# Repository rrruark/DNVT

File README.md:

# DNVT
Digital Non-secure Voice Terminal Test Code and Switch PCBA Design Files.

http://robruark.com/projects/DNVT/DNVT_overview.html

This repo contains the PCBA design files for the DNVT test interface boards, four phone switches which run Nick Andre's code, and the crappy support code I wrote to initially reverse engineering DNVTs. 

The Arduino code encodes and decodes Differential Manchester, and the Python scripts determine the codewords. There is also a Python script which decodes differential manchester based on a CSV capture from an oscilloscope. Example files are provided.

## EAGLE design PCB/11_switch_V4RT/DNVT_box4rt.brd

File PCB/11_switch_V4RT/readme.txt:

Eagle Schematic: DNVT_box3rt.sch
Eagle Layout: DNVT_box3rt.brd
Schematic PDF: DNVT_box3rt.pdf

JLCPCB Gerbers: DNVT_box3rt_2023-05-02.zip
JLCPCB Top Placement: DNVT_box3rt_top_cpl.csv
JLCPCB BOM: DNVT_box3rt_top_bom.csv

Through Hole BOM: DNVT_box3rt_th_bom.csv
Additional BOM: DNVT_box3r_aux_bom.csv

Notes:

-The JLCPCB BOM maps all surface mount parts and all through hole parts aside from the DC barrel jack and transformers to parts available in JLCPCB's parts library.
-The bottom side parts are optional (additional chassis ground to Pico Ground capacitors and uSD card holder)
-The Digikey BOM lists through hole parts (DC barrel jack and transformers) which must be manually assembled.
-The additional BOM lists parts not captured in the Eagle BOM export: the case, OLED screen, Front and back plates, screws, nuts, cable for screen, and 48V power supply.

Designer Contact: Robert Ruark: rob@robruark.com

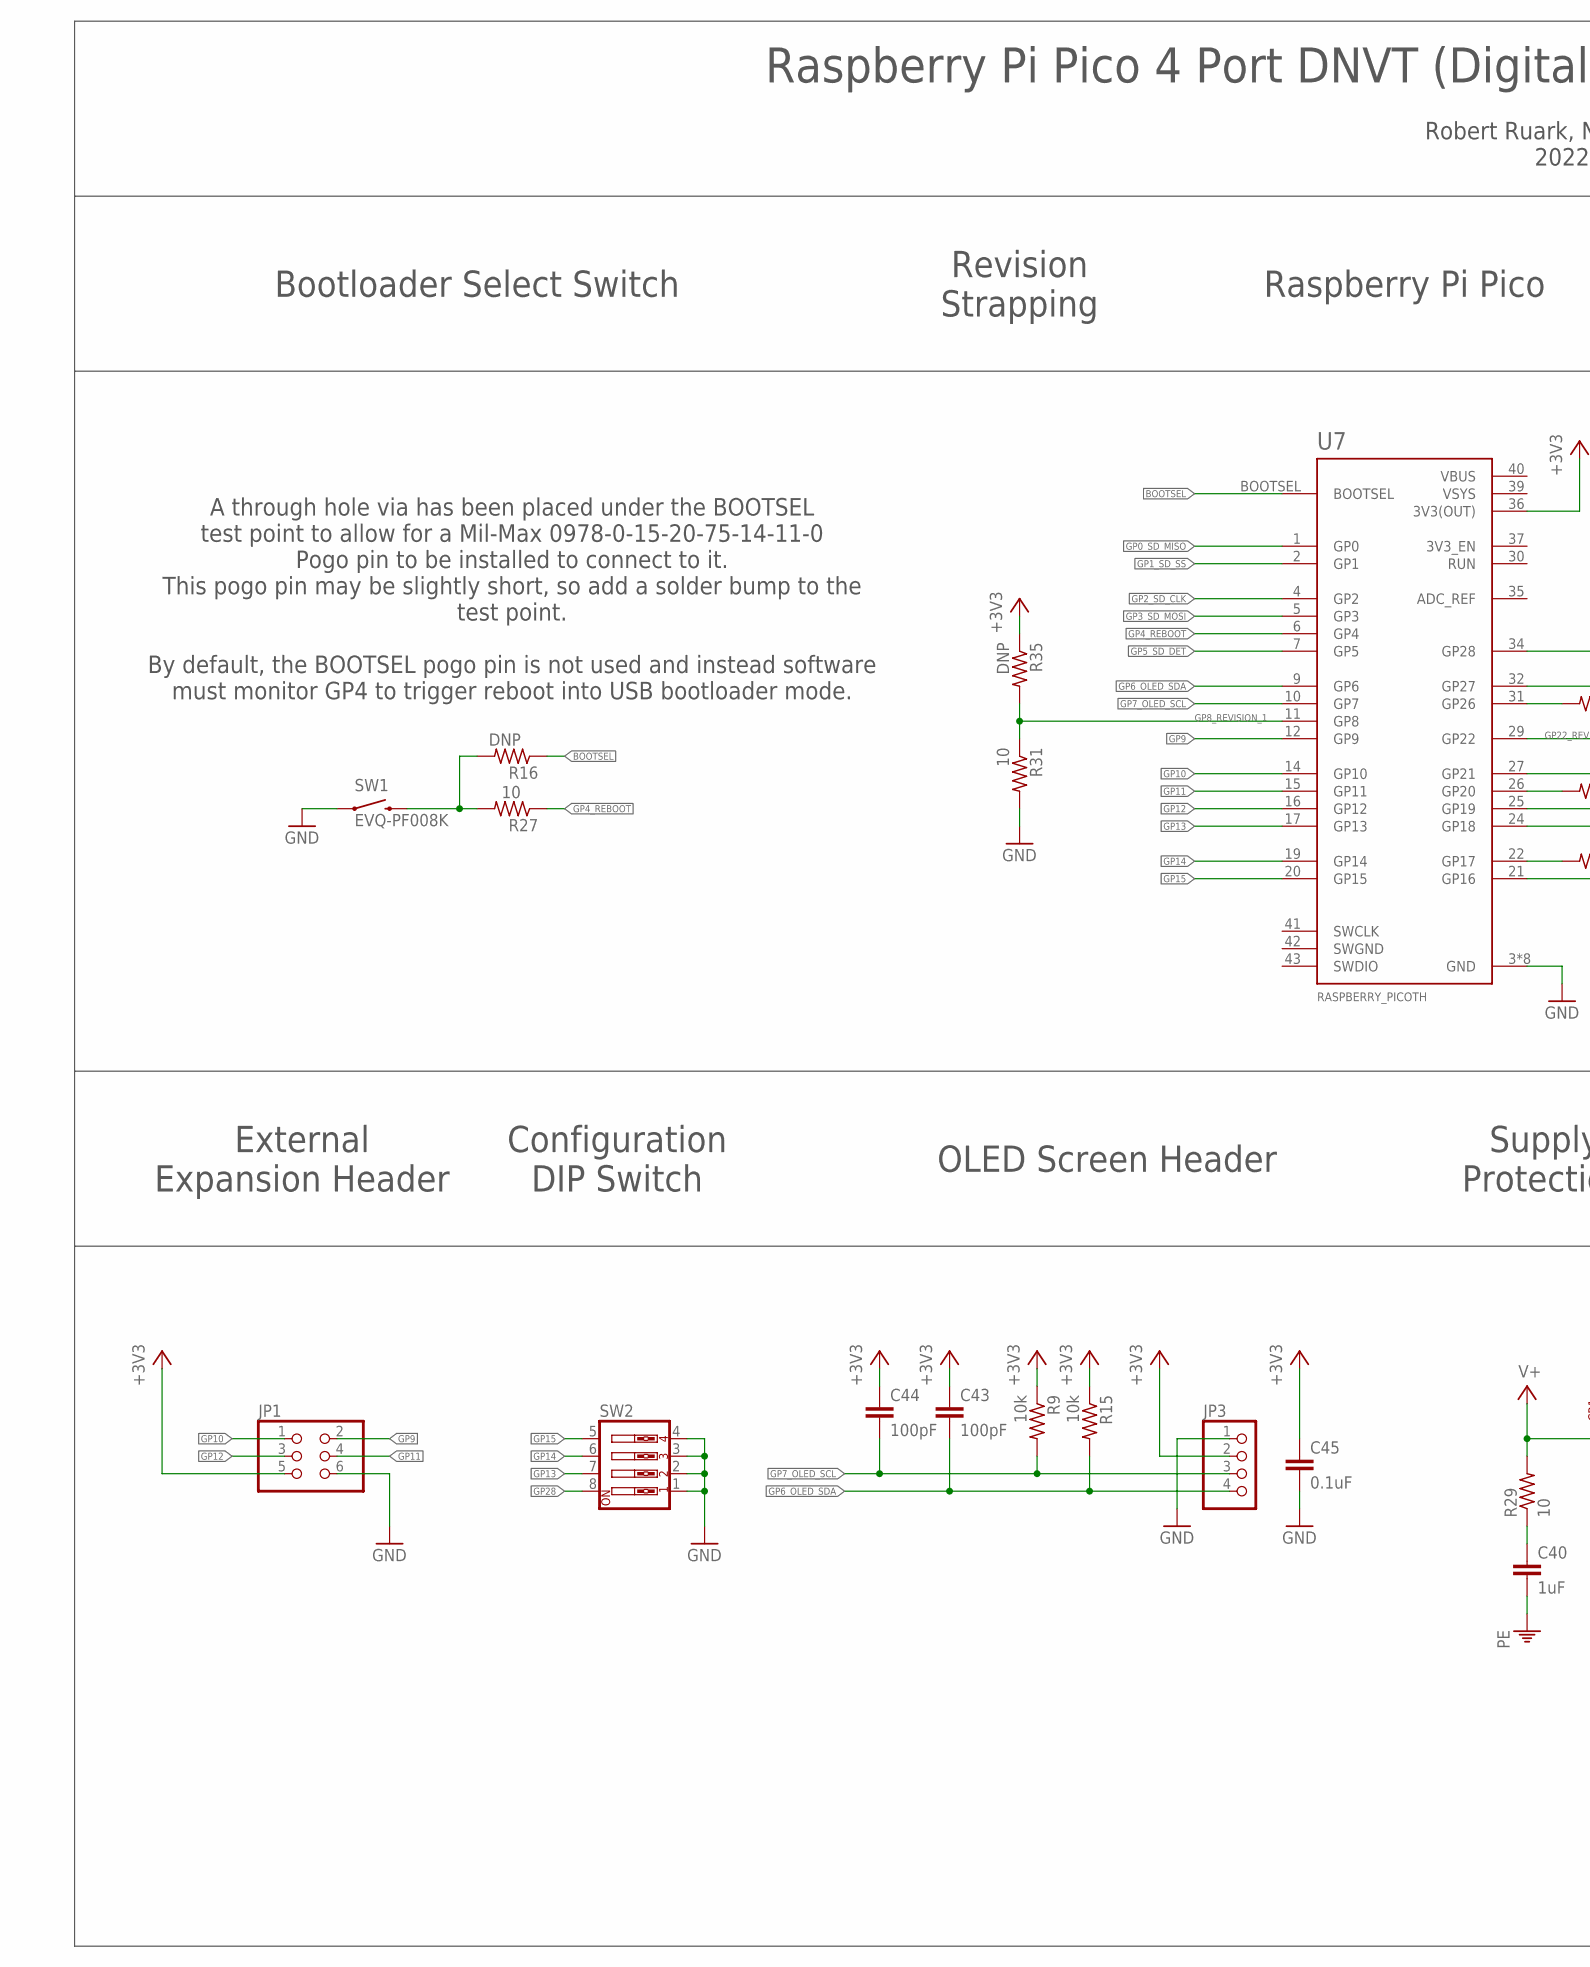
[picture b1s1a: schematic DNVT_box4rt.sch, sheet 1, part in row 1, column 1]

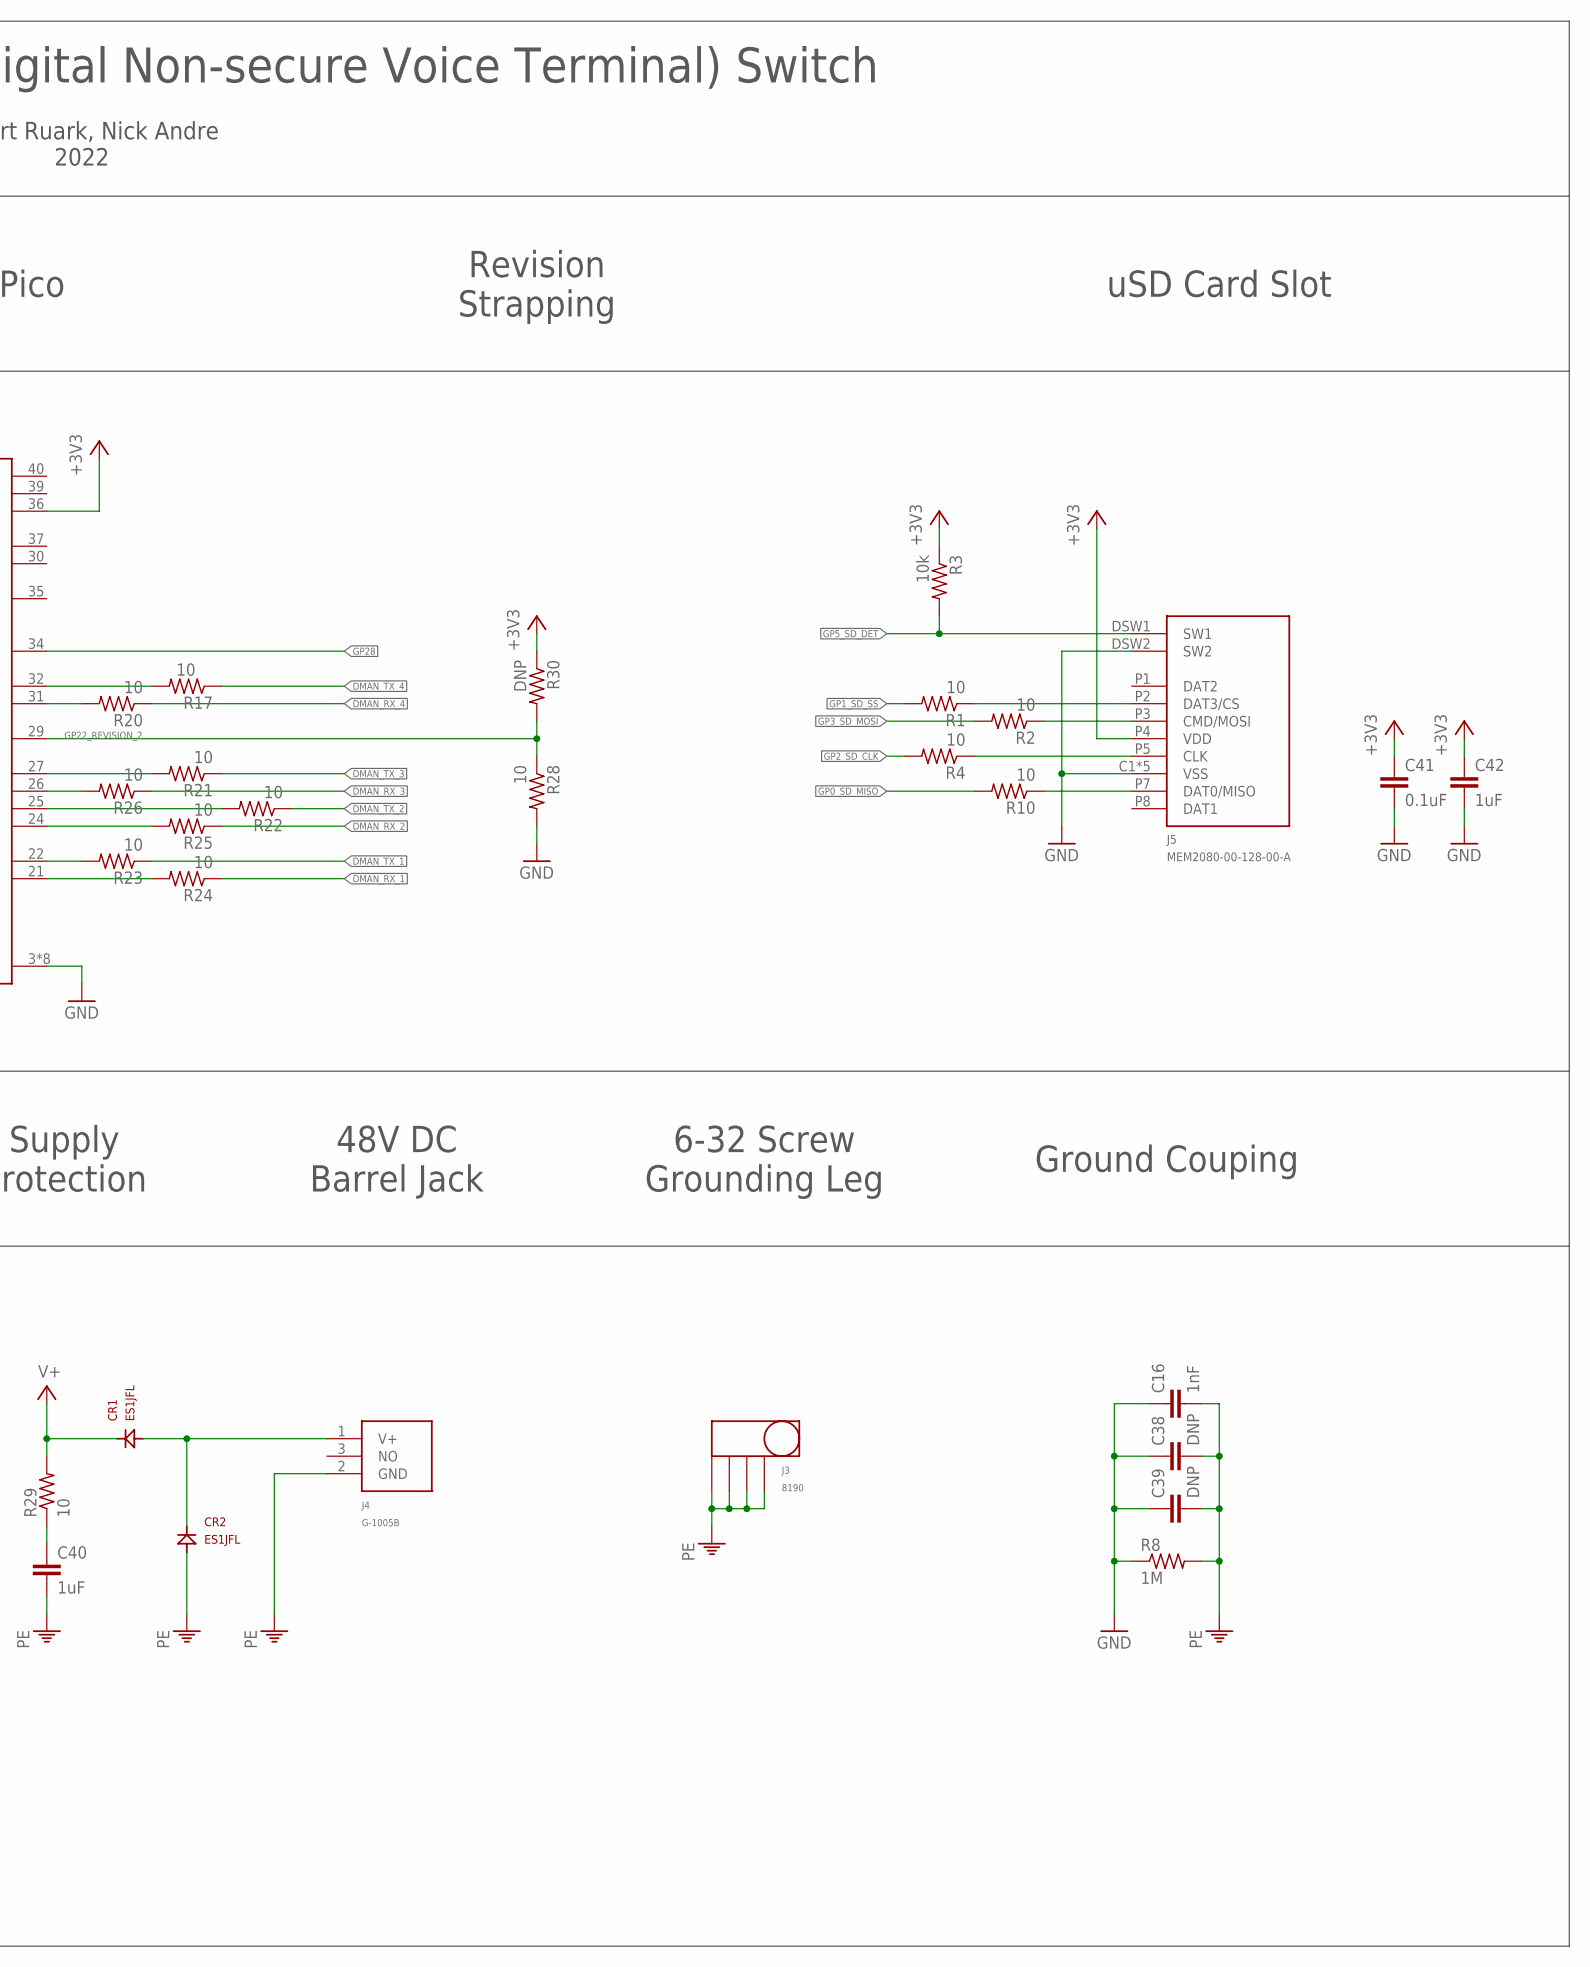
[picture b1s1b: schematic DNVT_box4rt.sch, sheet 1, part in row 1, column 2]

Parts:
C16: 1nF; 1206
C38, C39: DNP; 1206
C40: 1uF; 1206
C41, C45: 0.1uF; 0603
C42: 1uF; 0805
C43, C44: 100pF; 0603
CR1, CR2: ES1JFL; SOD123(AK)
J3: 8190; 7781
J4: G-1005B
J5: MEM2080-00-128-00-A; MEM2080
JP1: PINHD-2X3/90; 2X03/90
JP3: PINHD-1X4; 1X04
R1, R2, R4, R10, R17, R20, R21, R22, R23, R24, R25, R26, R27, R28, R31: 10; 0603
R3, R9, R15: 10k; 0603
R8: 1M; 1206
R16, R30, R35: DNP; 0603
R29: 10; 1206
SW1: EVQ-PF008K
SW2: SW_DIP-4; EDG-04
U7: RASPBERRY_PICOTH; PICO-PKG-TH

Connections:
+3V3: C41.1, C42.1, C43.1, C44.1, C45.1, J5.P4 (VDD), JP1.5, JP3.2, R3.1, R9.1, R15.1, R30.1, R35.1, U7.36 (3V3(OUT)); also elsewhere on the board
BOOTSEL: R16.1, U7.BOOTSEL
DMAN_RX_1: R24.1; also elsewhere on the board
DMAN_RX_2: R25.1; also elsewhere on the board
DMAN_RX_3: R26.1; also elsewhere on the board
DMAN_RX_4: R20.1; also elsewhere on the board
DMAN_TX_1: R23.1; also elsewhere on the board
DMAN_TX_2: R22.1; also elsewhere on the board
DMAN_TX_3: R21.1; also elsewhere on the board
DMAN_TX_4: R17.1; also elsewhere on the board
GND: C16.1, C38.1, C39.1, C41.2, C42.2, C45.2, J5.C1 (VSS), J5.C2 (VSS), J5.C3 (VSS), J5.C4 (VSS), J5.DSW2 (SW2), J5.P6 (VSS), JP1.6, JP3.1, R8.1, R28.2, R31.2, SW1.S1 (1), SW2.1, SW2.2, SW2.3, SW2.4, U7.3 (GND), U7.8 (GND), U7.13 (GND), U7.18 (GND), U7.23 (GND), U7.28 (GND), U7.33 (GND), U7.38 (GND); also elsewhere on the board
GP0_SD_MISO: R10.2, U7.1 (GP0)
GP1_SD_SS: R1.2, U7.2 (GP1)
GP2_SD_CLK: R4.2, U7.4 (GP2)
GP3_SD_MOSI: R2.2, U7.5 (GP3)
GP4_REBOOT: R27.1, U7.6 (GP4)
GP5_SD_DET: J5.DSW1 (SW1), R3.2, U7.7 (GP5)
GP6_OLED_SDA: C43.2, JP3.4, R15.2, U7.9 (GP6)
GP7_OLED_SCL: C44.2, JP3.3, R9.2, U7.10 (GP7)
GP8_REVISION_1: R31.1, R35.2, U7.11 (GP8)
GP9: JP1.2, U7.12 (GP9)
GP10: JP1.1, U7.14 (GP10)
GP11: JP1.4, U7.15 (GP11)
GP12: JP1.3, U7.16 (GP12)
GP13: SW2.7, U7.17 (GP13)
GP14: SW2.6, U7.19 (GP14)
GP15: SW2.5, U7.20 (GP15)
GP22_REVISION_2: R28.1, R30.2, U7.29 (GP22)
GP28: SW2.8, U7.34 (GP28)
unnamed: R20.2, U7.31 (GP26)
unnamed: R17.2, U7.32 (GP27)
unnamed: R24.2, U7.21 (GP16)
unnamed: R23.2, U7.22 (GP17)
unnamed: R16.2, R27.2, SW1.S2 (2)
unnamed: CR1.A, CR2.K, J4.1 (V+)
unnamed: R25.2, U7.24 (GP18)
unnamed: R22.2, U7.25 (GP19)
unnamed: R21.2, U7.27 (GP21)
unnamed: R26.2, U7.26 (GP20)
unnamed: J5.P5 (CLK), R4.1
unnamed: C40.1, R29.1
unnamed: J5.P7 (DAT0/MISO), R10.1
unnamed: J5.P3 (CMD/MOSI), R2.1
unnamed: J5.P2 (DAT3/CS), R1.1
PE: C16.2, C38.2, C39.2, C40.2, CR2.A, J3.P$1, J3.P$2, J3.P$3, J3.P$4, J4.2 (GND), R8.2; also elsewhere on the board
SWGND: U7.42 (SWGND)
V+: CR1.K, R29.2; also elsewhere on the board
VBUS: U7.40 (VBUS)
VSYS: U7.39 (VSYS)

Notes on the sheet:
Raspberry Pi Pico 4 Port DNVT (Digital Non-secure Voice Terminal) Switch
Robert Ruark, Nick Andre 2022
Raspberry Pi Pico
Ground Couping
External Expansion Header
OLED Screen Header
48V DC Barrel Jack
6-32 Screw Grounding Leg
A through hole via has been placed under the BOOTSEL test point to allow for a Mil-Max 0978-0-15-20-75-14-11-0 Pogo pin to be installed to connect to it. This pogo pin may be slightly short, so add a solder bump to the test point. By default, the BOOTSEL pogo pin is not used and instead software mu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
Configuration DIP Switch
Supply Protection
Revision Strapping
Bootloader Select Switch
uSD Card Slot

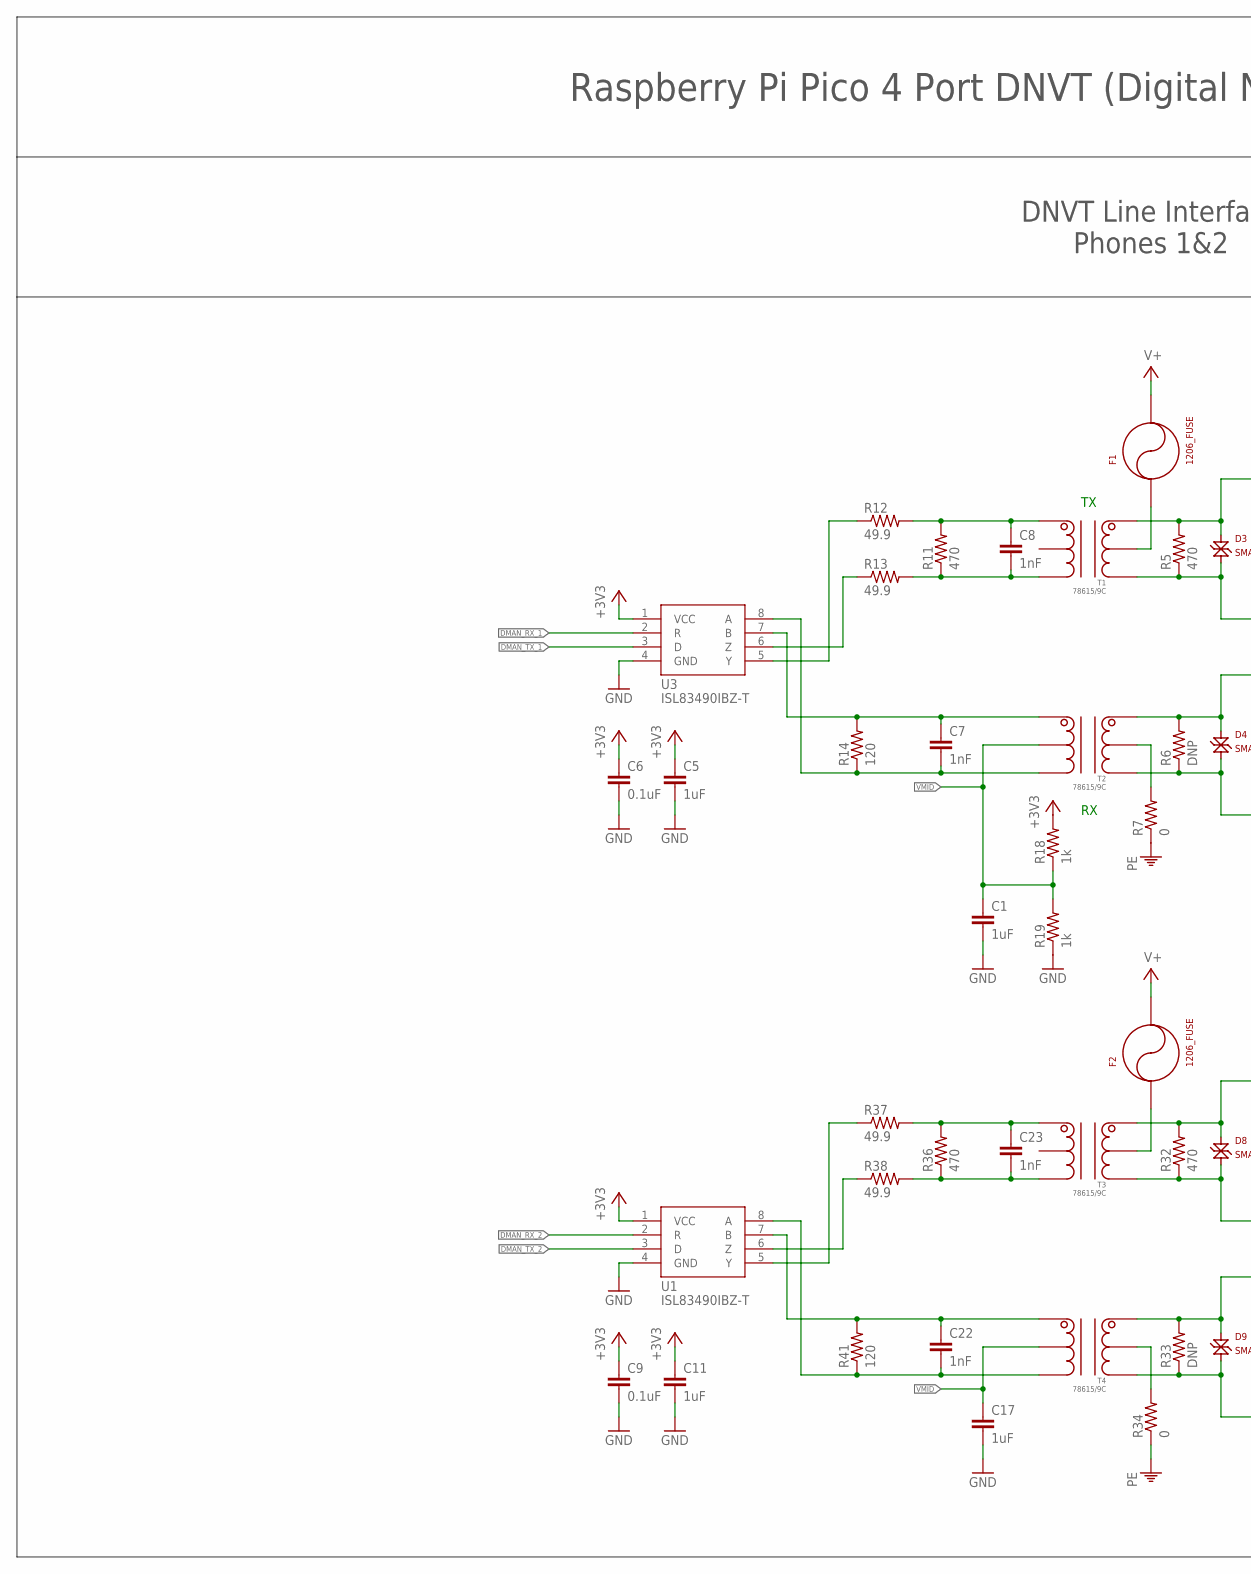
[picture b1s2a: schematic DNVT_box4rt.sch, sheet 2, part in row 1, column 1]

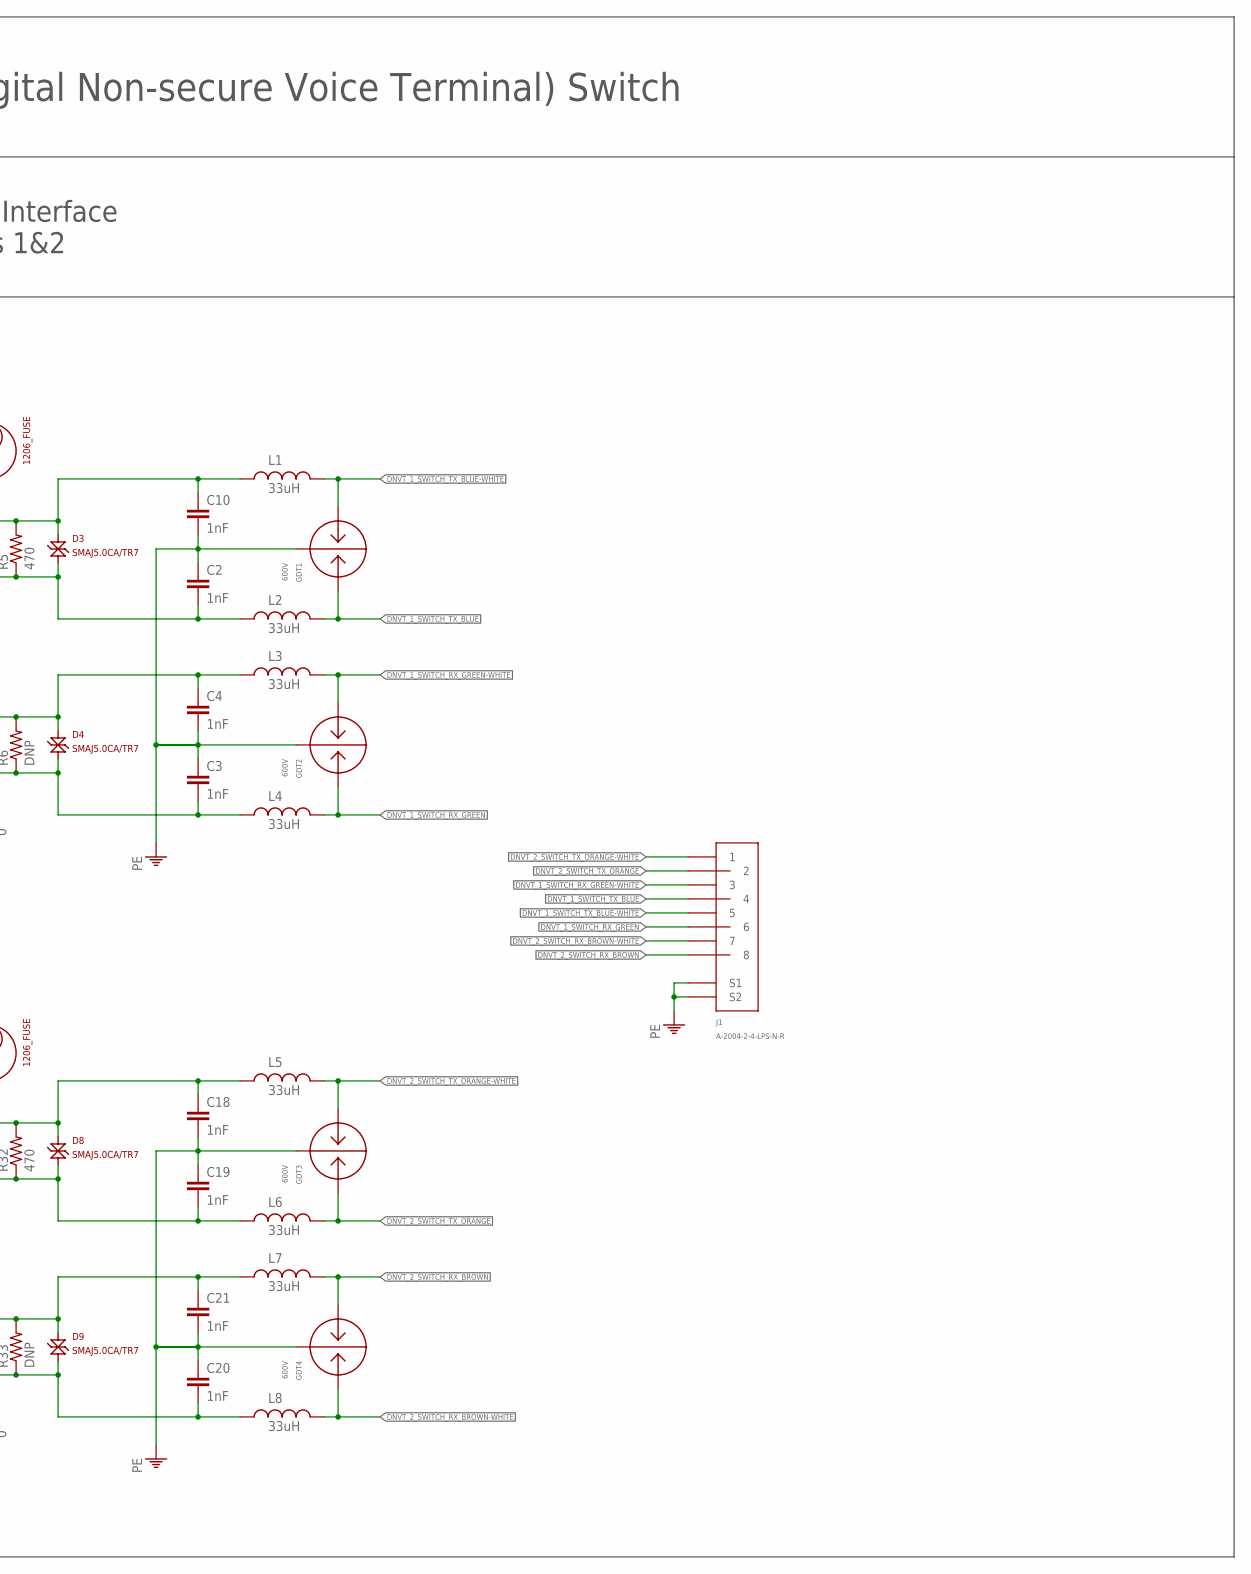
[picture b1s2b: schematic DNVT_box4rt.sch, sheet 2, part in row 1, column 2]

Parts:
C1, C5, C11, C17: 1uF; 0805
C2, C3, C4, C7, C8, C10, C18, C19, C20, C21, C22, C23: 1nF; 0805
C6, C9: 0.1uF; 0603
D3, D4, D8, D9: SMAJ5.0CA/TR7; DO-214AC_NO_POL
F1, F2: 1206_FUSE; 1206
GDT1, GDT2, GDT3, GDT4: 600V; 2036_GDT
J1: A-2004-2-4-LPS-N-R
L1, L2, L3, L4, L5, L6, L7, L8: 33uH; SDR0403
R5, R11, R32, R36: 470; R0805
R6, R33: DNP; R0805
R7, R34: 0; R0805
R12, R13, R37, R38: 49.9; R0805
R14, R41: 120; 1206
R18, R19: 1k; 0603
T1, T2, T3, T4: 78615/9C; 786T
U1, U3: ISL83490IBZ-T; SOIC8

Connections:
+3V3: C5.1, C6.1, C9.1, C11.1, R18.2, U1.1 (VCC), U3.1 (VCC); also elsewhere on the board
DMAN_RX_1: U3.2 (R); also elsewhere on the board
DMAN_RX_2: U1.2 (R); also elsewhere on the board
DMAN_TX_1: U3.3 (D); also elsewhere on the board
DMAN_TX_2: U1.3 (D); also elsewhere on the board
DNVT_1_SWITCH_RX_GREEN: GDT2.L2, J1.6, L4.2
DNVT_1_SWITCH_RX_GREEN-WHITE: GDT2.L1, J1.3, L3.2
DNVT_1_SWITCH_TX_BLUE: GDT1.L2, J1.4, L2.2
DNVT_1_SWITCH_TX_BLUE-WHITE: GDT1.L1, J1.5, L1.2
DNVT_2_SWITCH_RX_BROWN: GDT4.L1, J1.8, L7.2
DNVT_2_SWITCH_RX_BROWN-WHITE: GDT4.L2, J1.7, L8.2
DNVT_2_SWITCH_TX_ORANGE: GDT3.L2, J1.2, L6.2
DNVT_2_SWITCH_TX_ORANGE-WHITE: GDT3.L1, J1.1, L5.2
GND: C1.2, C5.2, C6.2, C9.2, C11.2, C17.2, R19.1, U1.4 (GND), U3.4 (GND); also elsewhere on the board
unnamed: C10.1, D3.C (K), L1.1, R5.2, T1.1
unnamed: C2.2, D3.A, L2.1, R5.1, T1.3
unnamed: C4.1, D4.C (K), L3.1, R6.2, T2.1
unnamed: C3.2, D4.A, L4.1, R6.1, T2.3
unnamed: R7.2, T2.2
unnamed: F1.1, T1.2
unnamed: C22.1, R41.2, T4.6, U1.7 (B)
unnamed: C7.1, R14.2, T2.6, U3.7 (B)
unnamed: C7.2, R14.1, T2.4, U3.8 (A)
unnamed: C8.2, R11.1, R13.2, T1.4
unnamed: C8.1, R11.2, R12.2, T1.6
unnamed: R12.1, U3.5 (Y)
unnamed: R13.1, U3.6 (Z)
unnamed: C22.2, R41.1, T4.4, U1.8 (A)
unnamed: C18.1, D8.C (K), L5.1, R32.2, T3.1
unnamed: C19.2, D8.A, L6.1, R32.1, T3.3
unnamed: C21.1, D9.C (K), L7.1, R33.2, T4.1
unnamed: C20.2, D9.A, L8.1, R33.1, T4.3
unnamed: R34.2, T4.2
unnamed: F2.1, T3.2
unnamed: C23.1, R36.2, R37.2, T3.6
unnamed: R37.1, U1.5 (Y)
unnamed: R38.1, U1.6 (Z)
unnamed: C23.2, R36.1, R38.2, T3.4
PE: C2.1, C3.1, C4.2, C10.2, C18.2, C19.1, C20.1, C21.2, GDT1.C, GDT2.C, GDT3.C, GDT4.C, J1.S1, J1.S2, R7.1, R34.1; also elsewhere on the board
V+: F1.2, F2.2; also elsewhere on the board
VMID: C1.1, C17.1, R18.1, R19.2, T2.5, T4.5; also elsewhere on the board

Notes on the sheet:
Raspberry Pi Pico 4 Port DNVT (Digital Non-secure Voice Terminal) Switch
DNVT Line Interface Phones 1&2

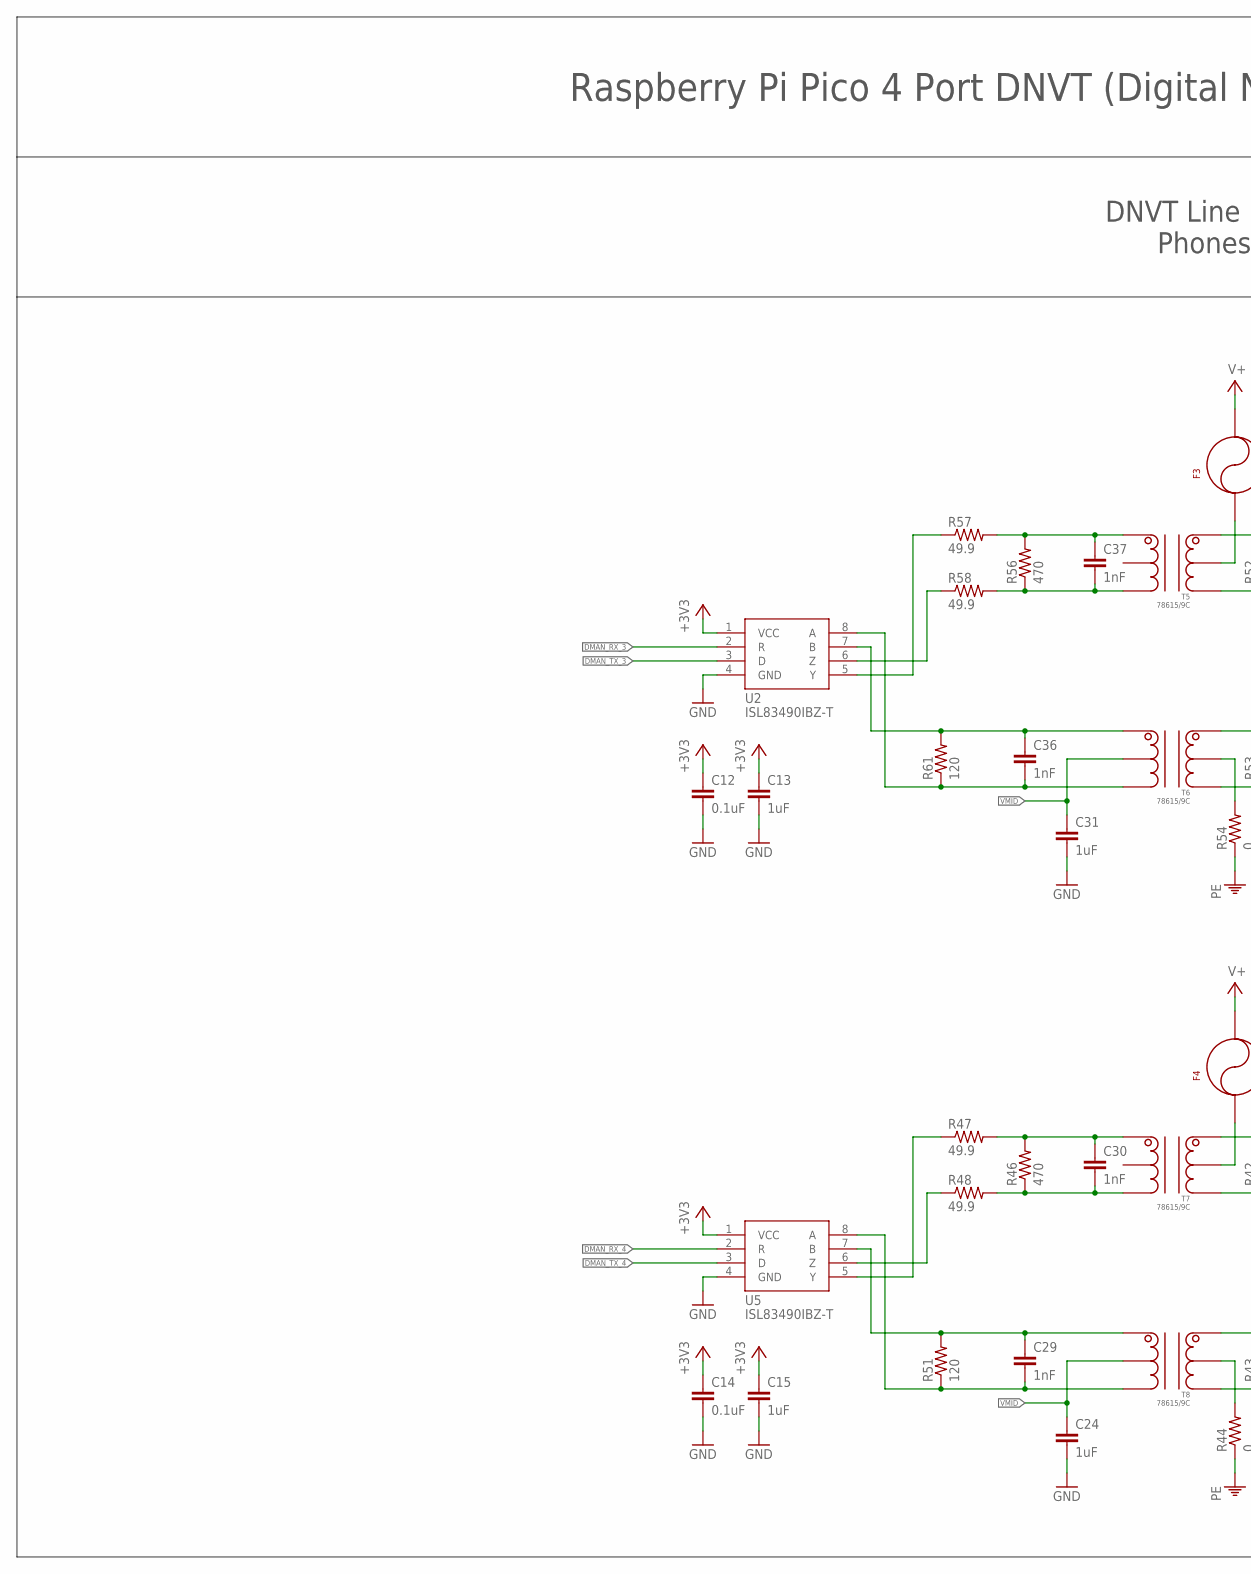
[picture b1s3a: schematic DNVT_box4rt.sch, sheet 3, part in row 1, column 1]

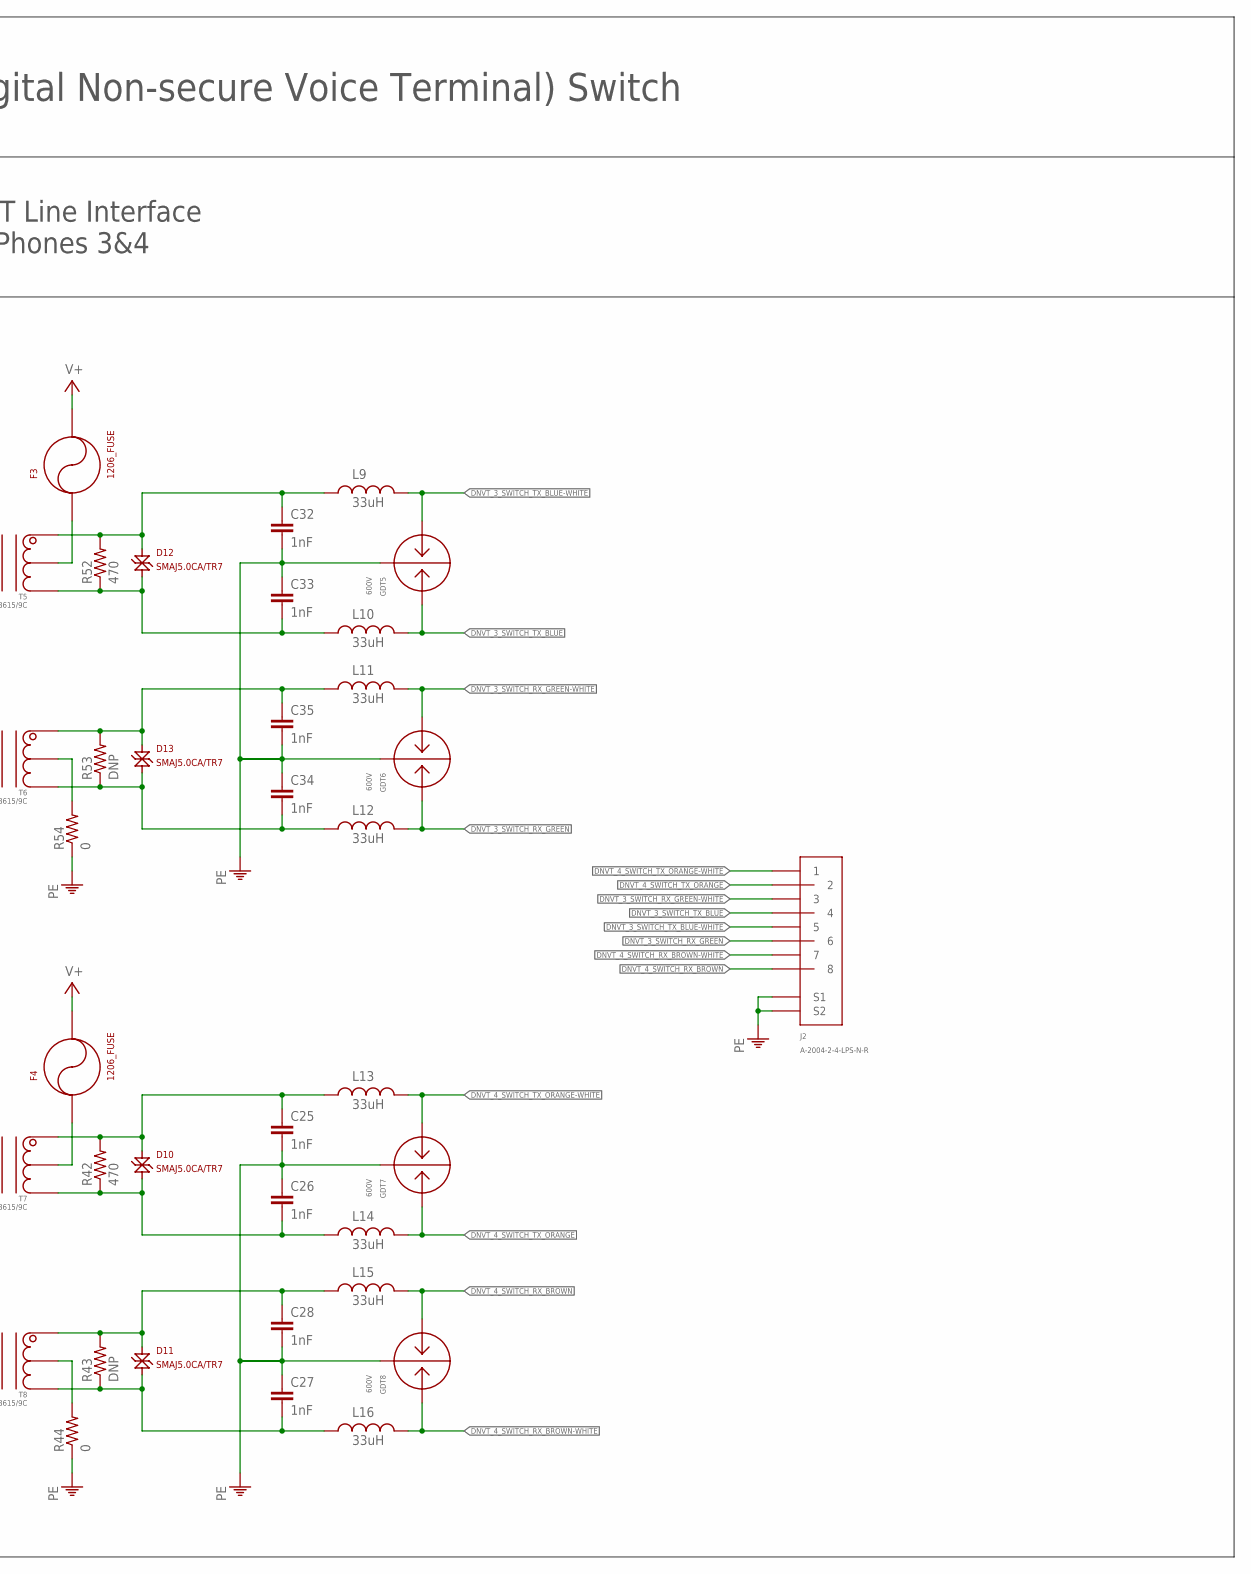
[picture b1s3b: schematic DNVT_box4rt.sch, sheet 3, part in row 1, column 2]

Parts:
C12, C14: 0.1uF; 0603
C13, C15, C24, C31: 1uF; 0805
C25, C26, C27, C28, C29, C30, C32, C33, C34, C35, C36, C37: 1nF; 0805
D10, D11, D12, D13: SMAJ5.0CA/TR7; DO-214AC_NO_POL
F3, F4: 1206_FUSE; 1206
GDT5, GDT6, GDT7, GDT8: 600V; 2036_GDT
J2: A-2004-2-4-LPS-N-R
L9, L10, L11, L12, L13, L14, L15, L16: 33uH; SDR0403
R42, R46, R52, R56: 470; R0805
R43, R53: DNP; R0805
R44, R54: 0; R0805
R47, R48, R57, R58: 49.9; R0805
R51, R61: 120; 1206
T5, T6, T7, T8: 78615/9C; 786T
U2, U5: ISL83490IBZ-T; SOIC8

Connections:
+3V3: C12.1, C13.1, C14.1, C15.1, U2.1 (VCC), U5.1 (VCC); also elsewhere on the board
DMAN_RX_3: U2.2 (R); also elsewhere on the board
DMAN_RX_4: U5.2 (R); also elsewhere on the board
DMAN_TX_3: U2.3 (D); also elsewhere on the board
DMAN_TX_4: U5.3 (D); also elsewhere on the board
DNVT_3_SWITCH_RX_GREEN: GDT6.L2, J2.6, L12.2
DNVT_3_SWITCH_RX_GREEN-WHITE: GDT6.L1, J2.3, L11.2
DNVT_3_SWITCH_TX_BLUE: GDT5.L2, J2.4, L10.2
DNVT_3_SWITCH_TX_BLUE-WHITE: GDT5.L1, J2.5, L9.2
DNVT_4_SWITCH_RX_BROWN: GDT8.L1, J2.8, L15.2
DNVT_4_SWITCH_RX_BROWN-WHITE: GDT8.L2, J2.7, L16.2
DNVT_4_SWITCH_TX_ORANGE: GDT7.L2, J2.2, L14.2
DNVT_4_SWITCH_TX_ORANGE-WHITE: GDT7.L1, J2.1, L13.2
GND: C12.2, C13.2, C14.2, C15.2, C24.2, C31.2, U2.4 (GND), U5.4 (GND); also elsewhere on the board
unnamed: C36.1, R61.2, T6.6, U2.7 (B)
unnamed: C36.2, R61.1, T6.4, U2.8 (A)
unnamed: C25.1, D10.C (K), L13.1, R42.2, T7.1
unnamed: C26.2, D10.A, L14.1, R42.1, T7.3
unnamed: C28.1, D11.C (K), L15.1, R43.2, T8.1
unnamed: C27.2, D11.A, L16.1, R43.1, T8.3
unnamed: R44.2, T8.2
unnamed: F4.1, T7.2
unnamed: C29.1, R51.2, T8.6, U5.7 (B)
unnamed: C30.1, R46.2, R47.2, T7.6
unnamed: R47.1, U5.5 (Y)
unnamed: R48.1, U5.6 (Z)
unnamed: C30.2, R46.1, R48.2, T7.4
unnamed: C29.2, R51.1, T8.4, U5.8 (A)
unnamed: C32.1, D12.C (K), L9.1, R52.2, T5.1
unnamed: C33.2, D12.A, L10.1, R52.1, T5.3
unnamed: C35.1, D13.C (K), L11.1, R53.2, T6.1
unnamed: C34.2, D13.A, L12.1, R53.1, T6.3
unnamed: R54.2, T6.2
unnamed: F3.1, T5.2
unnamed: C37.1, R56.2, R57.2, T5.6
unnamed: R57.1, U2.5 (Y)
unnamed: R58.1, U2.6 (Z)
unnamed: C37.2, R56.1, R58.2, T5.4
PE: C25.2, C26.1, C27.1, C28.2, C32.2, C33.1, C34.1, C35.2, GDT5.C, GDT6.C, GDT7.C, GDT8.C, J2.S1, J2.S2, R44.1, R54.1; also elsewhere on the board
V+: F3.2, F4.2; also elsewhere on the board
VMID: C24.1, C31.1, T6.5, T8.5; also elsewhere on the board

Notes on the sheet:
Raspberry Pi Pico 4 Port DNVT (Digital Non-secure Voice Terminal) Switch
DNVT Line Interface Phones 3&4

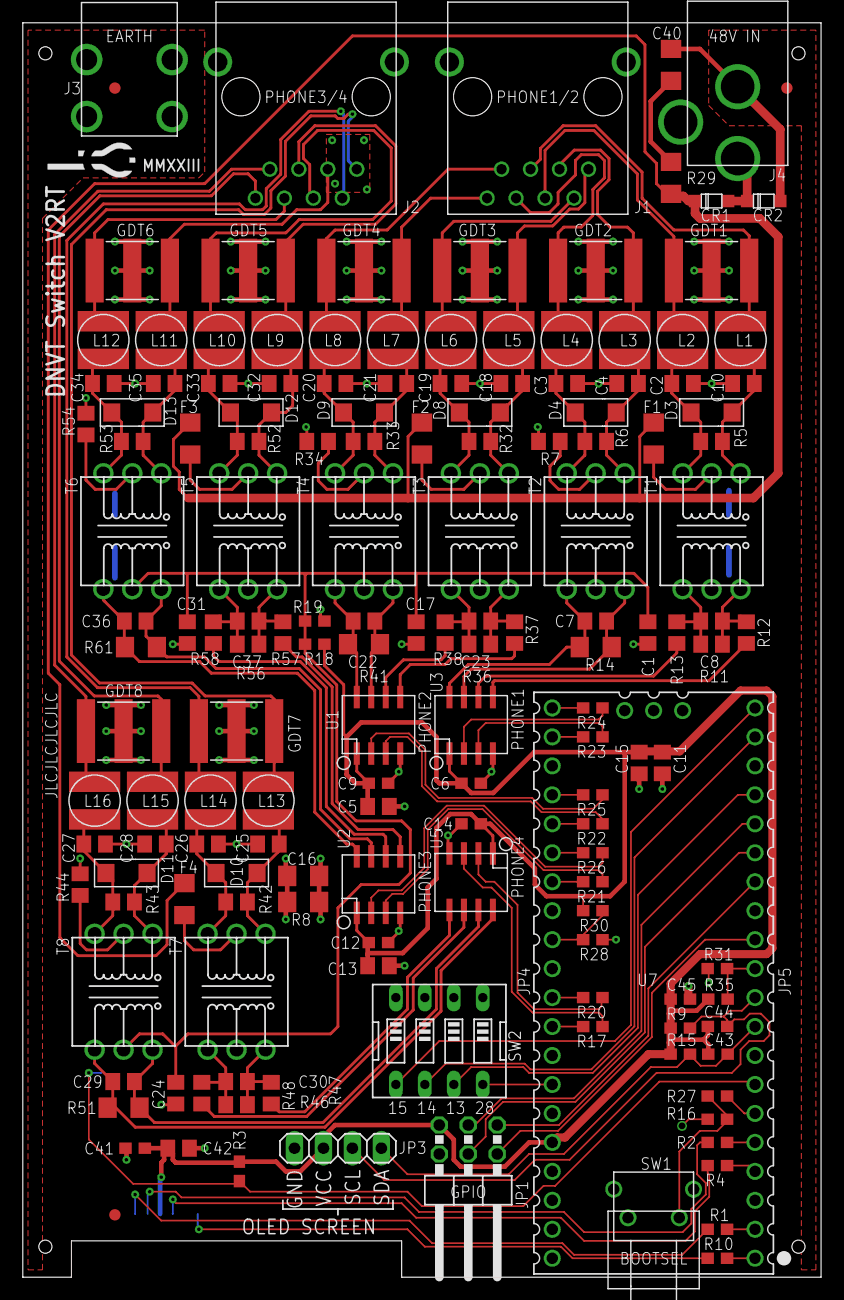
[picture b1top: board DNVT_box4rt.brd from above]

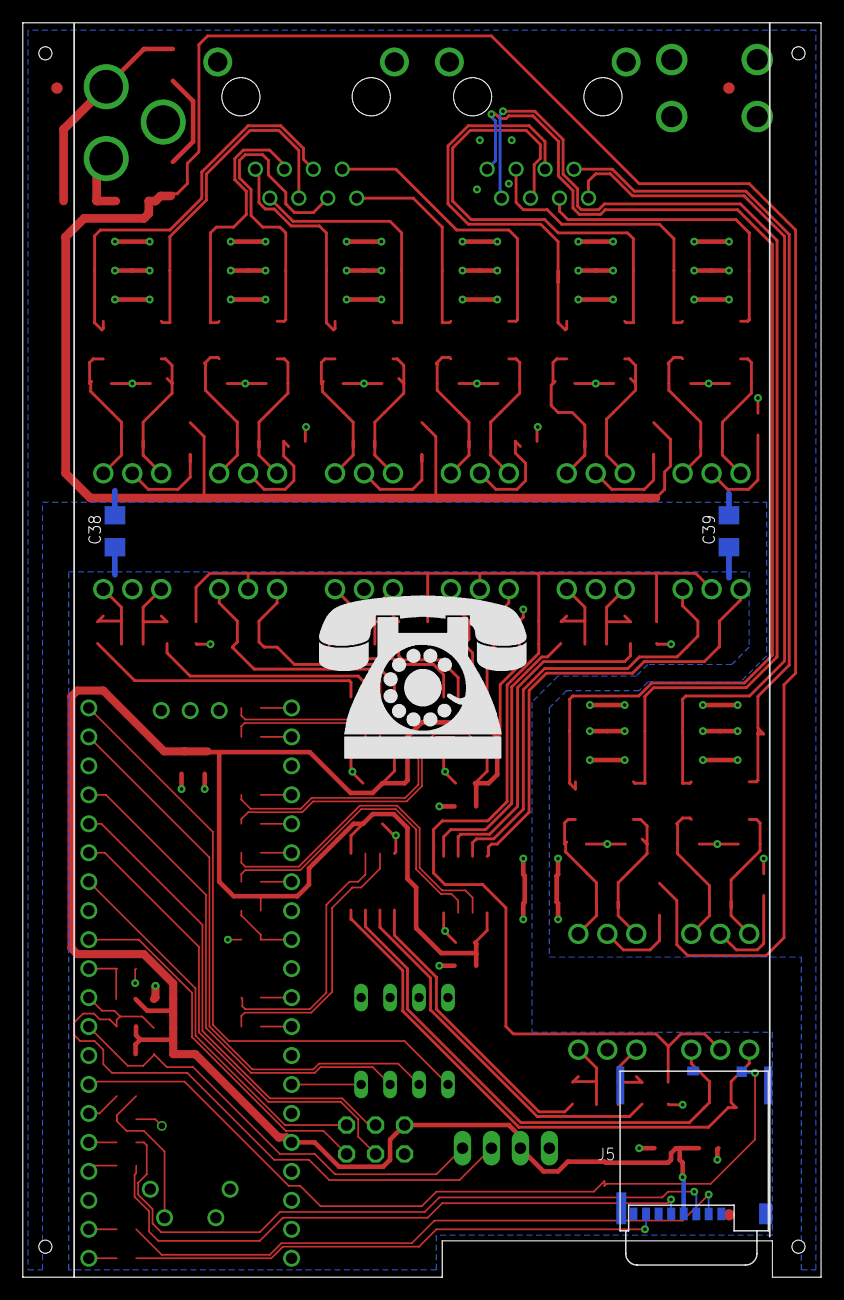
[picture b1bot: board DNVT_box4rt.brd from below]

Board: 2 copper layers, 70.0 x 110.0 mm, 158 parts (3 on the bottom side), 111 nets.

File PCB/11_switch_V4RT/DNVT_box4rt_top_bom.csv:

Comment,Designator,Footprint,LCSC Part #
0,R7 R34 R44 R54,R0805,
0.1uF,C6 C9 C12 C14 C41 C45,603,
1M,R8,1206,C17927
1k,R18 R19,603,
1nF,C2 C3 C4 C7 C8 C10,805,
1nF,C16,1206,C9196
1nF,C18 C19 C20 C21 C22 C23 C25 C26 C27 C28 C29 C30 C32 C33 C34 C35 C36 C37,805,
1uF,C1 C5 C11 C13 C15 C17 C24 C31,805,
1uF,C40,1206,
1uF,C42,805,
10,R1 R2 R4 R10 R17 R20 R21 R22 R23 R24 R25 R26 R27 R28,603,
10,R29,1206,
10,R31,603,
10k,R3 R9 R15,603,
33uH,L1 L2 L3 L4 L5 L6 L7 L8 L9 L10 L11 L12 L13 L14 L15 L16,SDR0403,C341014
49.9,R12 R13 R37 R38 R47 R48 R57 R58,R0805,
100pF,C43 C44,603,
120,R14 R41 R51 R61,1206,
470,R5 R11 R32 R36 R42 R46 R52 R56,R0805,
600V,GDT1 GDT2 GDT3 GDT4 GDT5 GDT6 GDT7 GDT8,2036_GDT,C2908079
1206_FUSE,F1 F2 F3 F4,1206,C135333
ES1JFL,CR1 CR2,SOD123(AK),C64898
ISL83490IBZ-T,U1 U2 U3 U5,SOIC8,C2932177
SMAJ5.0CA/TR7,D3 D4 D8 D9 D10 D11 D12 D13,DO-214AC_NO_POL,C78402
RJ45,J1 J2,,C3010550
Welding terminal,J3,7779 or 8190,C238168
6 pin header,JP1,,C2935935
4 pin header,JP3,,C2691448
20 pin header,JP4 JP5,,C429947
RA tactile sw,SW1,,C2845272
4 dip switch,SW2,,C962226
